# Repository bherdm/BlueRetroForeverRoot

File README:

# BlueRetroForeverRoot
Root repository to sync esp-idf and BlueRetroForever versions.

BlueRetroForever is an active fork of the archived [BlueRetro](https://github.com/darthcloud/BlueRetro)
by Jacques Gagnon — see that repo for the original project's documentation.

## Repository layout (read this first)

Three repositories nest here. Know which is which:

| Repo | What it is | You edit it? |
|---|---|---|
| **BlueRetroForever** (this submodule) | The ESP32 firmware source — the actual code. Default branch **`main`** carries the ongoing work (N64 keyboard/mouse, etc.). | **Yes — this is the code.** |
| **esp-idf** (this submodule) | Espressif's SDK + Xtensa toolchain. The firmware *cannot compile without it*. Pinned to a specific commit that matches the CI image. | No |
| **BlueRetroForeverRoot** (this repo) | A build-harness superproject. Its only job: pin one firmware commit + one matching esp-idf commit together (so a build is reproducible) and provide the `blueretro_dev.sh` environment + setup guides. | Only to bump the pinned versions |

Mental model: **root** = "which firmware + which SDK, wired together"; **BlueRetroForever** = the
source you change; **esp-idf** = the compiler. Develop in the `BlueRetroForever/` submodule (on
`main`); bump this root's submodule pointer when you want to publish a new known-good pairing:

```bash
git submodule update --remote BlueRetroForever   # advance the firmware pointer to origin/main
git add BlueRetroForever && git commit -m "BlueRetro ref <version>"
```

# Development instructions

[Instructions for Ubuntu 20.04+](#blueretro-development-on-ubuntu-2004)\
[Instructions for macOS 13+](README.macos)\
[Instructions for Windows 10+](README.windows)

These instructions likely mostly apply for older version and/or different distribution as well.
But they are not tested, so YMMV and you're on your own.

# BlueRetro development on Ubuntu 20.04+

## 1 - Initial setup

### 1.1 - Install ESP-IDF Prerequisites
1. Open a Terminal (like gnome-terminal or konsole).
2. Do the following command:
   ```bash
   sudo apt-get install git wget flex bison gperf python3 python3-pip python3-venv cmake ninja-build ccache libffi-dev libssl-dev dfu-util libusb-1.0-0
   ```

### 1.2 - BlueRetro code checkout
1. Open a Terminal (like gnome-terminal or konsole).
3. Do the following commands:
   ```bash
   cd ~
   git clone https://github.com/bherdm/BlueRetroForeverRoot.git
   cd ~/BlueRetroForeverRoot/
   git submodule update --init --recursive
   export IDF_TOOLS_PATH=$(pwd)
   cd esp-idf
   ./install.sh
   ```

##  2 - Compiling BlueRetro firmware
1. Open a Terminal (like gnome-terminal or konsole).
3. Do the following commands:
   ```bash
   cd ~/BlueRetroRoot/
   . ./blueretro_dev.sh
   cd BlueRetroForever
   # Replace configs/hw1/universal by any other config you may wish
   cp configs/hw1/universal sdkconfig
   idf.py build
   # Replace serial device with your own
   idf.py -p /dev/ttyUSB0 flash
   idf.py -p /dev/ttyUSB0 monitor
   ```

# ESP32 embedded development tips

## Dump spiffs
```bash
esptool.py --chip esp32 read_flash 0x310000 0xF0000 spiffs.bin
mkspiffs.exe -u spiffs_unpack -b 4096 -p 256 -s 0xF0000 .\spiffs.bin
```

## Delete spiffs
```bash
esptool.py erase_region 0x310000 0xF0000
```

## QEMU
```bash
(cd build; esptool.py --chip esp32 merge_bin --fill-flash-size 4MB -o flash_image.bin @flash_args)
```
```bash
qemu-system-xtensa -machine esp32 -drive file=build/flash_image.bin,if=mtd,format=raw -serial stdio -display none -nic user,model=open_eth,id=lo0,hostfwd=tcp:127.0.0.1:8001-:80
```

## Running GitHub action offline

Using [github.com/nektos/act](https://github.com/nektos/act)

Checkout main repo separately, then:
```bash
act -W .github/workflows/quick.yml --input hw_version=hw1 --input br_config=universal --artifact-server-path /tmp
```

<!-- vim: set syntax=Markdown: -->

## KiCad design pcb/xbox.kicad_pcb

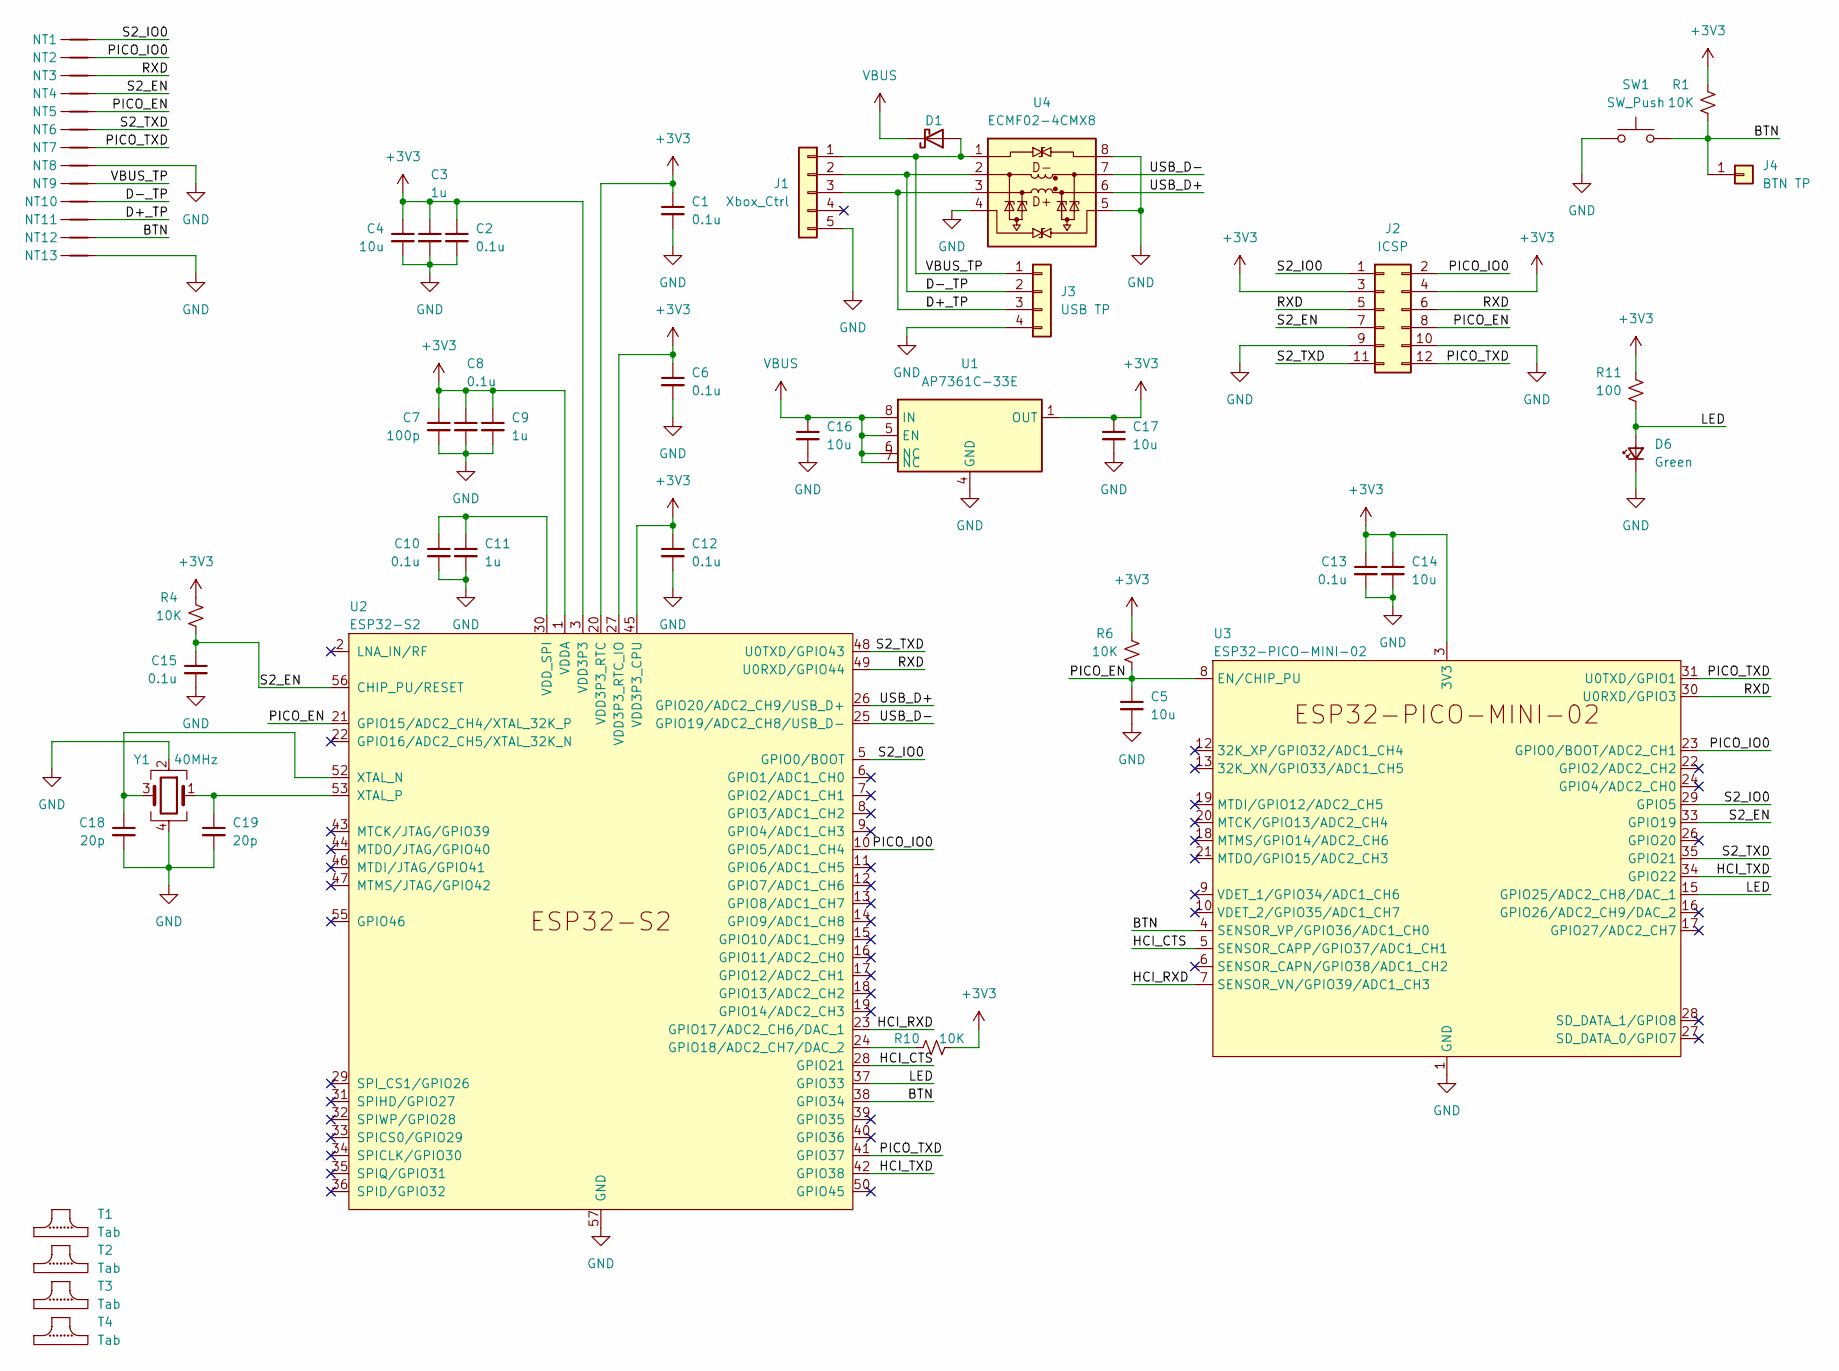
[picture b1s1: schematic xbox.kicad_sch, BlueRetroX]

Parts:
C1, C2, C6, C8, C10, C12, C13, C15: 0.1u; C_0201_0603Metric; Digikey 587-5831-2-ND
C3, C9, C11: 1u; C_0201_0603Metric; Digikey 490-GRM032R60J105ME05DTR-ND
C4, C5, C14, C16, C17: 10u; C_0402_1005Metric; Digikey 490-GRM155R60J106ME05JTR-ND
C7: 100p; C_0201_0603Metric; Digikey 490-GRM033R71E101JA01DTR-ND
C18, C19: 20p; C_0402_1005Metric; Digikey 490-11315-2-ND
D1: PMEG6010ESBYL; DSN1006-2_0.6x1mm_P0.65mm; Digikey 1727-2401-2-ND
D6: Green; LED_0603_1608Metric; Digikey 160-1478-2-ND
J1: Xbox_Ctrl; Xbox_PinHeader_1x05_P2.00mm_Vertical; Digikey DNP
J2: ICSP; PinHeader_2x06_P1.00mm; Digikey DNP
J3: USB TP; PinHeader_1x04_P1.00mm_Vertical; Digikey DNP
J4: BTN TP; TestPoint_1x01
NT1, NT2, NT3, NT4, NT5, NT6, NT7, NT8, NT9, NT10, NT11, NT12, NT13: NetTie; NetTie_SMD_Pad0.12mm
R1, R4, R6, R10: 10K; R_0402_1005Metric; Digikey 311-10.0KMTR-ND
R11: 100; R_0402_1005Metric; Digikey 311-100MTR-ND
SW1: SW_Push; SW_SPST_B3U-3000P; Digikey SW1022TR-ND
T1, T2, T3, T4: Tab; Digikey DNP
U1: AP7361C-33E; U-DFN3030-8E_3x3mm_P0.65mm_EP1.5x2.25mm; Digikey AP7361C-33FGE-7DITR-ND
U2: ESP32-S2; QFN-56-1EP_7x7mm_P0.4mm_EP5.6x5.6mm; Digikey 1965-ESP32-S2FN4R2TR-ND
U3: ESP32-PICO-MINI-02; Digikey 1965-ESP32-PICO-MINI-02-N8R2TR-ND
U4: ECMF02-4CMX8; UQFN-8L_2.5x1.2mm_P0.5mm; Digikey 497-13420-2-ND
Y1: 40MHz; Crystal_SMD_2016-4Pin_2.0x1.6mm; Digikey FW400WFMR1TR-ND

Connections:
+3V3: C1.1, C2.1, C3.1, C4.1, C6.1, C7.1, C8.1, C9.1, C12.1, C13.1, C14.1, C17.1, J2.3, J2.4, R1.2, R4.2, R6.2, R10.2, R11.2, U1.1 (OUT), U2.1 (VDDA), U2.3 (VDD3P3), U2.4 (VDD3P3), U2.20 (VDD3P3_RTC), U2.27 (VDD3P3_RTC_IO), U2.45 (VDD3P3_CPU), U2.51 (VDDA), U2.54 (VDDA), U3.3 (3V3)
/BTN: J4.1, NT12.1, R1.1, SW1.1, U2.38 (GPIO34), U3.4 (SENSOR_VP/GPIO36/ADC1_CH0)
/D+_TP: J1.3, J3.3, NT11.1, U4.3 (D+_in)
/D-_TP: J1.2, J3.2, NT10.1, U4.2 (D-_in)
/HCI_CTS: U2.28 (GPIO21), U3.5 (SENSOR_CAPP/GPIO37/ADC1_CH1)
/HCI_RXD: U2.23 (GPIO17/ADC2_CH6/DAC_1), U3.7 (SENSOR_VN/GPIO39/ADC1_CH3)
/HCI_TXD: U2.42 (GPIO38), U3.34 (GPIO22)
/LED: D6.2 (A), R11.1, U2.37 (GPIO33), U3.15 (GPIO25/ADC2_CH8/DAC_1)
/PICO_EN: C5.1, J2.8, NT5.1, R6.1, U2.21 (GPIO15/ADC2_CH4/XTAL_32K_P), U3.8 (EN/CHIP_PU)
/PICO_IO0: J2.2, NT2.1, U2.10 (GPIO5/ADC1_CH4), U3.23 (GPIO0/BOOT/ADC2_CH1)
/PICO_TXD: J2.12, NT7.1, U2.41 (GPIO37), U3.31 (U0TXD/GPIO1)
/RXD: J2.5, J2.6, NT3.1, U2.49 (U0RXD/GPIO44), U3.30 (U0RXD/GPIO3)
/S2_EN: C15.1, J2.7, NT4.1, R4.1, U2.56 (CHIP_PU/RESET), U3.33 (GPIO19)
/S2_IO0: J2.1, NT1.1, U2.5 (GPIO0/BOOT), U3.29 (GPIO5)
/S2_TXD: J2.11, NT6.1, U2.48 (U0TXD/GPIO43), U3.35 (GPIO21)
/USB_D+: U2.26 (GPIO20/ADC2_CH9/USB_D+), U4.6 (D+_out)
/USB_D-: U2.25 (GPIO19/ADC2_CH8/USB_D-), U4.7 (D-_out)
/VBUS_TP: D1.2 (A), J1.1, J3.1, NT9.1, U4.1 (VBUS)
GND: C1.2, C2.2, C3.2, C4.2, C5.2, C6.2, C7.2, C8.2, C9.2, C10.2, C11.2, C12.2, C13.2, C14.2, C15.2, C16.2, C17.2, C18.2, C19.2, D6.1 (K), J1.5, J2.9, J2.10, J3.4, NT8.1, NT13.1, SW1.2, U1.4 (GND), U1.9 (GND), U2.57 (GND), U3.1 (GND), U3.2 (GND), U3.11 (GND), U3.14 (GND), U3.36 (GND), U3.37 (GND), U3.38 (GND), U3.39 (GND), U3.40 (GND), U3.41 (GND), U3.42 (GND), U3.43 (GND), U3.44 (GND), U3.45 (GND), U3.46 (GND), U3.47 (GND), U3.48 (GND), U3.49 (GND), U3.50 (GND), U3.51 (GND), U3.52 (GND), U3.53 (GND), U4.4 (ID), U4.5 (GND), U4.8 (GND), Y1.2, Y1.4
unnamed: R10.1, U2.24 (GPIO18/ADC2_CH7/DAC_2)
unnamed: C10.1, C11.1, U2.30 (VDD_SPI)
unnamed: C18.1, U2.52 (XTAL_N), Y1.3
unnamed: C19.1, U2.53 (XTAL_P), Y1.1
VBUS: C16.1, D1.1 (K), U1.5 (EN), U1.6 (NC), U1.7 (NC), U1.8 (IN)

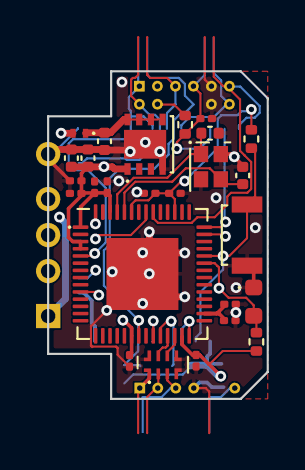
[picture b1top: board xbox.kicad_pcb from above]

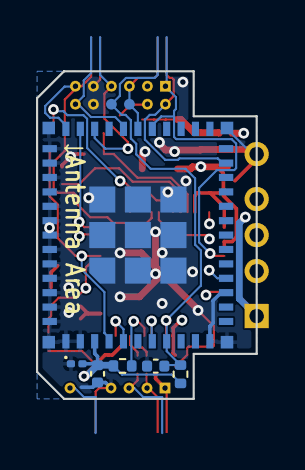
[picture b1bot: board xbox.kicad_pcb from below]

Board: 4 copper layers, 12.2 x 18.2 mm, 53 parts (13 on the bottom side), 24 nets.

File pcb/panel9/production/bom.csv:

Designator,Footprint,Quantity,Value,LCSC Part #
"_42, _41, _40, _39, _38, _37, _36, _35, _34, _33, _32, _31, _30, _29, _28, _27, _26, _25, _24, _23, _22, _21, _20, _19, _18, _17, _16, _15, _14, _13, _12, _11, _10, _9, _8, _7, _6, _5, _4, _3, _2, ",,42,,
"C1_6, C1_5, C1_4, C1_3, C1_2, C1, C10_6, C10_5, C10_4, C10_3, C10_2, C10, C12_6, C12_5, C12_4, C12_3, C12_2, C12, C13_6, C13_5, C13_4, C13_3, C13_2, C13, C15_6, C15_5, C15_4, C15_3, C15_2, C15, C2_6, C2_5, C2_4, C2_3, C2_2, C2, C6_6, C6_5, C6_4, C6_3, C6_2, C6, C8_6, C8_5, C8_4, C8_3, C8_2, C8",0201,48,0.1u,C76928
"C11_6, C11_5, C11_4, C11_3, C11_2, C11, C3_6, C3_5, C3_4, C3_3, C3_2, C3, C9_6, C9_5, C9_4, C9_3, C9_2, C9",0201,18,1u,C237458
"C14_6, C14_5, C14_4, C14_3, C14_2, C14, C16_6, C16_5, C16_4, C16_3, C16_2, C16, C17_6, C17_5, C17_4, C17_3, C17_2, C17, C4_6, C4_5, C4_4, C4_3, C4_2, C4, C5_6, C5_5, C5_4, C5_3, C5_2, C5",0402,30,10u,C15525
"C18_6, C18_5, C18_4, C18_3, C18_2, C18, C19_6, C19_5, C19_4, C19_3, C19_2, C19",0402,12,20p,C1554
"C7_6, C7_5, C7_4, C7_3, C7_2, C7",0201,6,100p,C161485
"D1_6, D1_5, D1_4, D1_3, D1_2, D1",DSN1006-2_0.6x1mm_P0.65mm,6,PMEG6010ESBYL,C552935
"D6_6, D6_5, D6_4, D6_3, D6_2, D6",0603,6,Green,C125113
"J1_6, J1_5, J1_4, J1_3, J1_2, J1",Xbox_PinHeader_1x05_P2.00mm_Vertical,6,Xbox_Ctrl,DNP
"J2_6, J2_5, J2_4, J2_3, J2_2, J2",PinHeader_2x06_P1.00mm,6,ICSP,DNP
"J3_6, J3_5, J3_4, J3_3, J3_2, J3",PinHeader_1x04_P1.00mm_Vertical,6,USB TP,DNP
"J4_6, J4_5, J4_4, J4_3, J4_2, J4",TestPoint_1x01,6,BTN TP,
"KIKIT_FID_B_1, KIKIT_FID_B_2, KIKIT_FID_B_3, KIKIT_FID_B_4, KIKIT_FID_T_1, KIKIT_FID_T_2, KIKIT_FID_T_3, KIKIT_FID_T_4",Fiducial,8,Fiducial,
"KIKIT_TO_1, KIKIT_TO_2, KIKIT_TO_3, KIKIT_TO_4",NPTH,4,NPTH,
"R1_6, R1_5, R1_4, R1_3, R1_2, R1, R10_6, R10_5, R10_4, R10_3, R10_2, R10, R4_6, R4_5, R4_4, R4_3, R4_2, R4, R6_6, R6_5, R6_4, R6_3, R6_2, R6",0402,24,10K,C25744
"R11_6, R11_5, R11_4, R11_3, R11_2, R11",0402,6,100,C25076
"SW1_6, SW1_5, SW1_4, SW1_3, SW1_2, SW1",SW_SPST_B3U-3000P,6,SW_Push,C963349
"U1_6, U1_5, U1_4, U1_3, U1_2, U1",U-DFN3030-8E_3x3mm_P0.65mm_EP1.5x2.25mm,6,AP7361C-33E,C151007
"U2_6, U2_5, U2_4, U2_3, U2_2, U2",QFN-56-1EP_7x7mm_P0.4mm_EP5.6x5.6mm,6,ESP32-S2,C2844252
"U3_6, U3_5, U3_4, U3_3, U3_2, U3",ESP32-PICO-MINI-02,6,ESP32-PICO-MINI-02,C2980306
"U4_6, U4_5, U4_4, U4_3, U4_2, U4",UQFN-8L_2.5x1.2mm_P0.5mm,6,ECMF02-4CMX8,C717678
"Y1_6, Y1_5, Y1_4, Y1_3, Y1_2, Y1",Crystal_SMD_2016-4Pin_2.0x1.6mm,6,40MHz,C2875288

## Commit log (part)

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2024-09-19 Xbox dev
2024-09-19 Add flash scripts
2024-09-19 add s2 update repo
2024-09-19 add pico update repo
2024-09-19 update ref radio
2024-09-19 xbox beta nosec
2024-09-19 add radio repo
2024-09-19 update ignore for xbox
2024-09-19 Update s2_fw_update ref
2024-09-29 Add script to build all FWs for XBOX
2024-10-01 xbox release v24.10
2024-11-09 Start picocom after flash S2
2024-11-09 Move flash bin into a folder
2025-12-14 Update BRX ref
2025-12-14 Update submodule URL
2025-12-14 Add link to brx docs
2025-12-14 Add kicad files
2025-12-14 Add BRX notes in README
2025-12-14 Add encryption disable info
2025-12-14 Enhance README with build and setup instructions
    Updated commands and added setup instructions for BlueRetro.
2025-12-14 Fix formatting in README for ESP32-S2 flash command
2025-12-20 Update BlueRetro submodule URL and specify branch to BlueRetroForever
2025-12-20 root: rename firmware submodule to BlueRetroForever
    Also update docs/.gitignore and bump the pinned firmware submodule to v25.10-beta-18-g2d9646d.
2026-01-15 Directed target submodule to BlueRetroForever's main branch.

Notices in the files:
pcb/xbox.kicad_sch:
©2024-2025 Jacques Gagnon, licensed under CC-BY-4.0
